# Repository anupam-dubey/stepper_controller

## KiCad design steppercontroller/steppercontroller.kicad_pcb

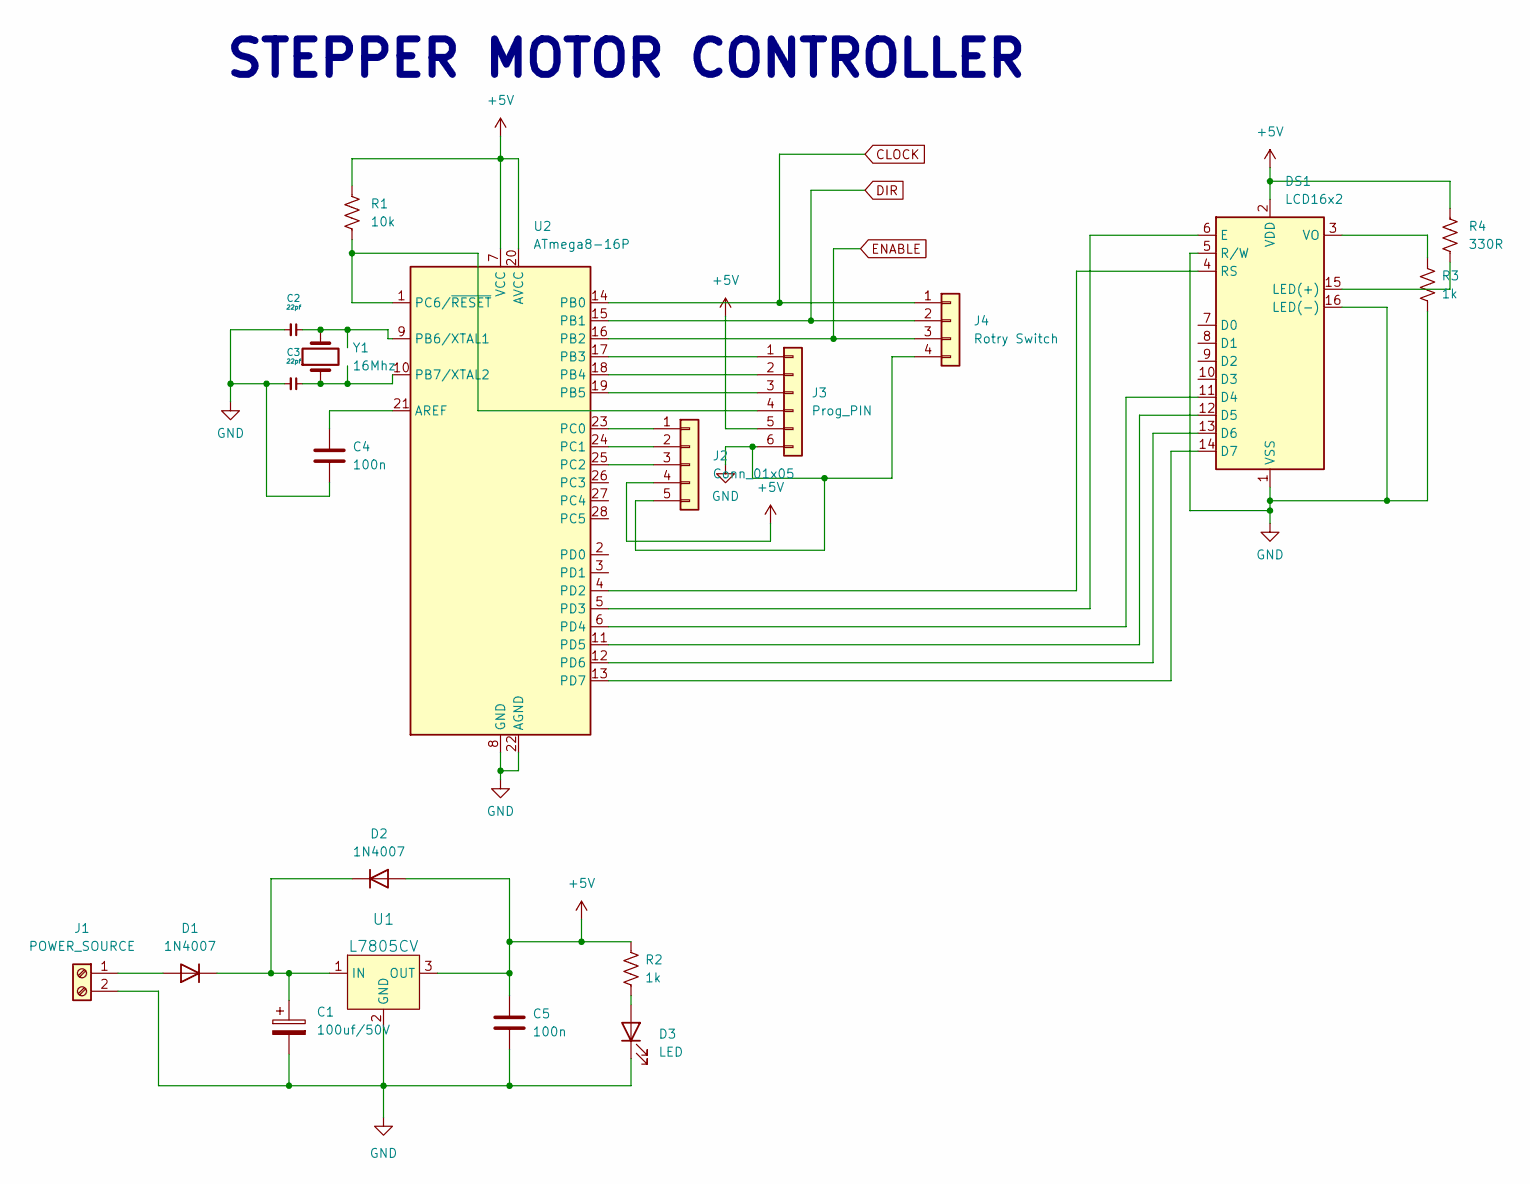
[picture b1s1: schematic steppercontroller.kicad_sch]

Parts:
C1: 100uf/50V; CP_Radial_D8.0mm_P3.80mm
C2, C3: 22pf; C_Disc_D4.3mm_W1.9mm_P5.00mm
C4, C5: 100n; C_Disc_D4.3mm_W1.9mm_P5.00mm
D1, D2: 1N4007; D_DO-41_SOD81_P10.16mm_Horizontal
D3: LED; LED_D5.0mm_FlatTop
DS1: LCD16x2; WC1602A
J1: POWER_SOURCE; TerminalBlock_Phoenix_MKDS-1,5-2-5.08_1x02_P5.08mm_Horizont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
J2: Conn_01x05; PinHeader_1x05_P2.54mm_Vertical
J3: Prog_PIN; PinHeader_1x06_P2.54mm_Vertical
J4: Rotry Switch; PinHeader_1x04_P2.54mm_Vertical
R1: 10k; R_Axial_DIN0207_L6.3mm_D2.5mm_P10.16mm_Horizontal
R2, R3: 1k; R_Axial_DIN0207_L6.3mm_D2.5mm_P10.16mm_Horizontal
R4: 330R; R_Axial_DIN0207_L6.3mm_D2.5mm_P10.16mm_Horizontal
U1: L7805CV; TO-220-3; MPN L7805CV; Digi-Key_PN 497-1443-5-ND
U2: ATmega8-16P; DIP-28_W7.62mm_LongPads
Y1: 16Mhz; Crystal_HC49-4H_Vertical

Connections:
+5V: C5.1, D2.2 (A), DS1.2 (VDD), J2.4, J3.5, R1.1, R2.1, R4.1, U1.3 (OUT), U2.7 (VCC), U2.20 (AVCC)
CLOCK: J4.1, U2.14 (PB0)
DIR: J4.2, U2.15 (PB1)
ENABLE: J4.3, U2.16 (PB2)
GND: C1.2, C2.2, C3.2, C4.2, C5.2, D3.1 (K), DS1.1 (VSS), DS1.5 (R/W), DS1.16 (LED(-)), J1.2, J2.5, J3.6, J4.4, R3.2, U1.2 (GND), U2.8 (GND), U2.22 (AGND)
unnamed: C1.1, D1.1 (K), D2.1 (K), U1.1 (IN)
unnamed: C2.1, U2.9 (PB6/XTAL1), Y1.2
unnamed: C3.1, U2.10 (PB7/XTAL2), Y1.1
unnamed: C4.1, U2.21 (AREF)
unnamed: D1.2 (A), J1.1
unnamed: D3.2 (A), R2.2
unnamed: DS1.3 (VO), R3.1
unnamed: DS1.4 (RS), U2.4 (PD2)
unnamed: DS1.6 (E), U2.5 (PD3)
unnamed: DS1.11 (D4), U2.6 (PD4)
unnamed: DS1.12 (D5), U2.11 (PD5)
unnamed: DS1.13 (D6), U2.12 (PD6)
unnamed: DS1.14 (D7), U2.13 (PD7)
unnamed: DS1.15 (LED(+)), R4.2
unnamed: J2.1, U2.23 (PC0)
unnamed: J2.2, U2.24 (PC1)
unnamed: J2.3, U2.25 (PC2)
unnamed: J3.1, U2.17 (PB3)
unnamed: J3.2, U2.18 (PB4)
unnamed: J3.3, U2.19 (PB5)
unnamed: J3.4, R1.2, U2.1 (PC6/~RESET)

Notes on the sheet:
STEPPER MOTOR CONTROLLER

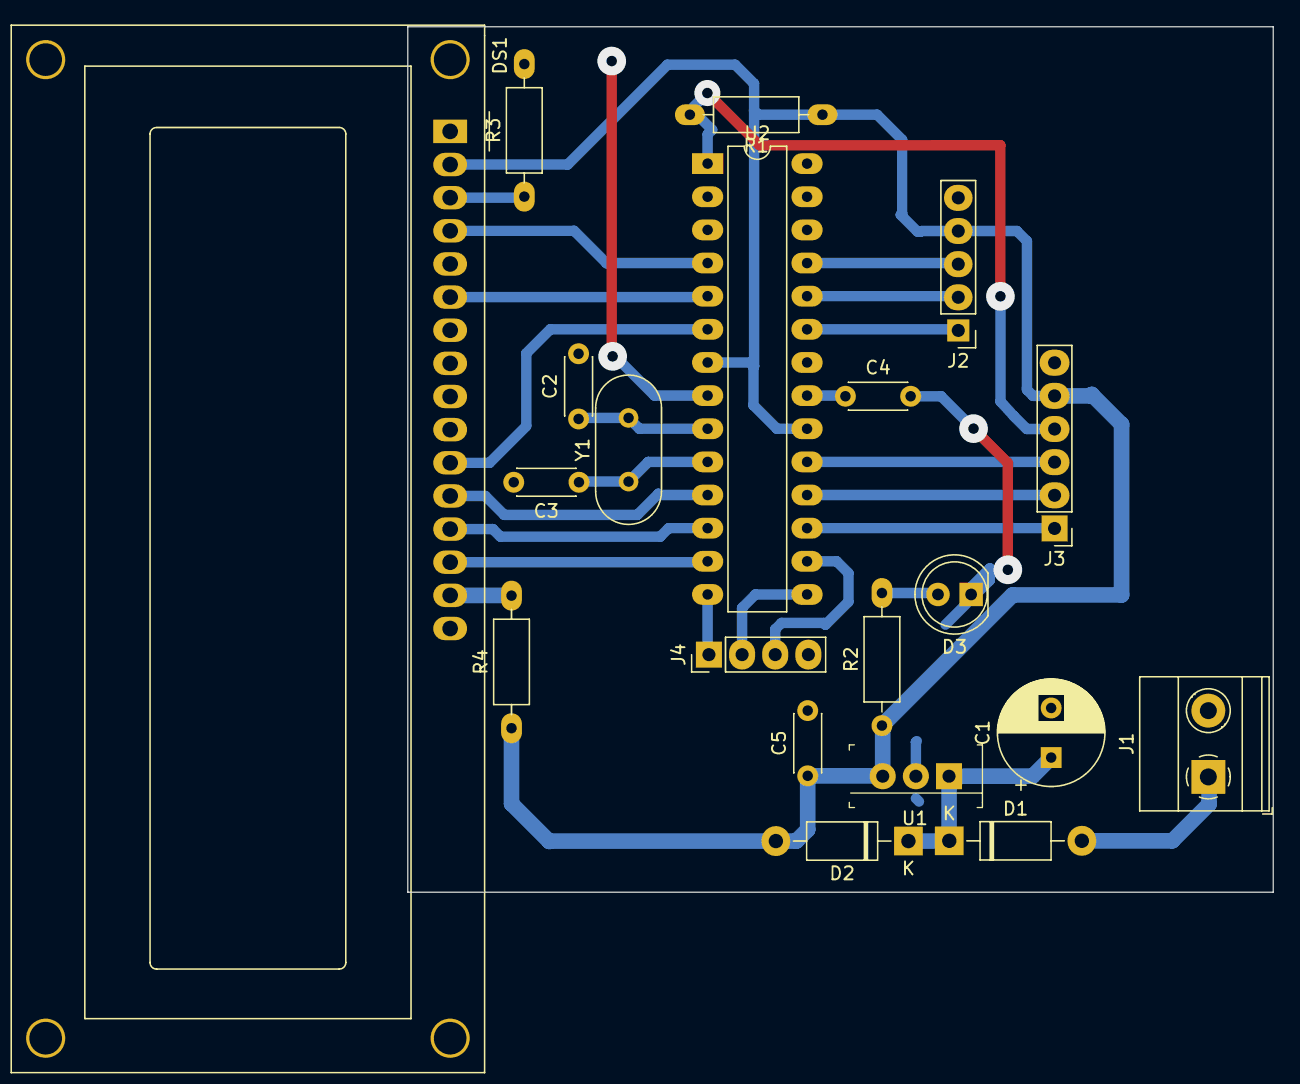
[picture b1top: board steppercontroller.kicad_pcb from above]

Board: 2 copper layers, 66.3 x 66.3 mm, 20 parts (0 on the bottom side), 26 nets.

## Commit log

2022-12-17 first
